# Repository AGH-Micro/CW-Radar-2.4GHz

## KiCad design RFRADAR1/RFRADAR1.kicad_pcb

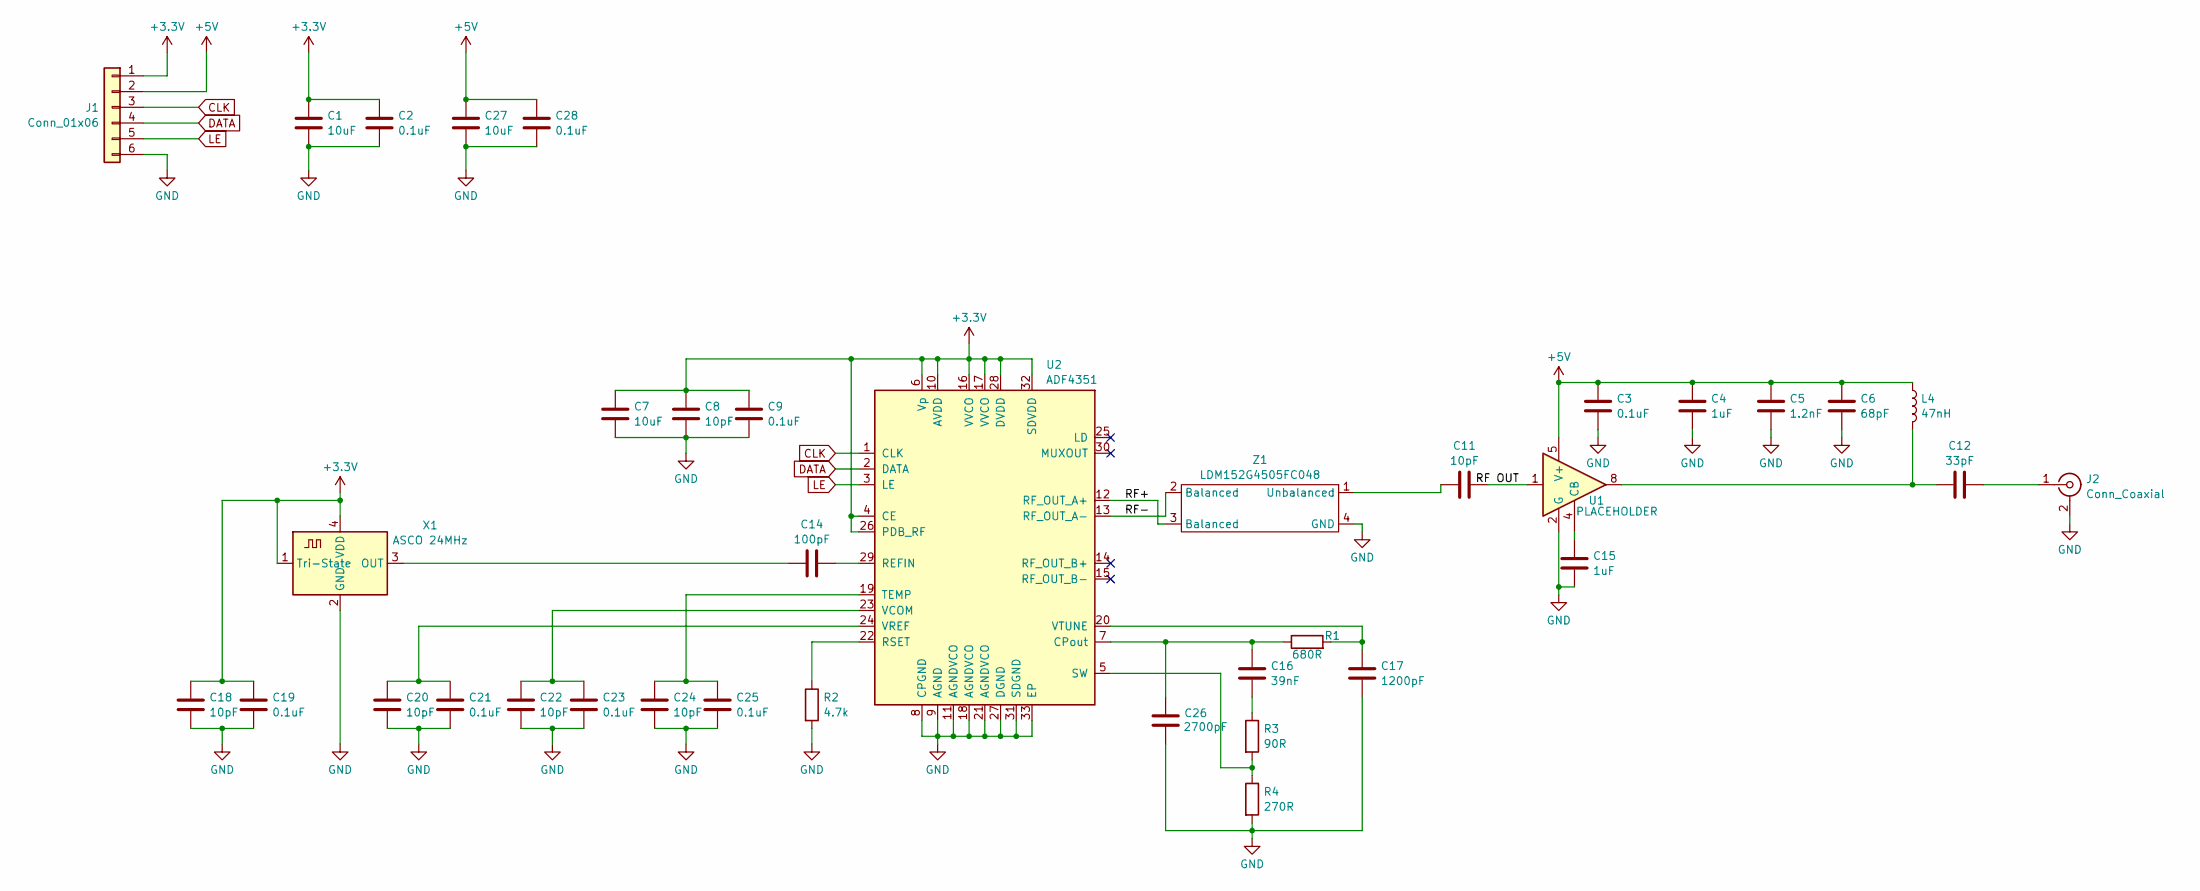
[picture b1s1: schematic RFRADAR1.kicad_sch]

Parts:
C1, C7, C27: 10uF; C_0402_1005Metric_Pad0.74x0.62mm_HandSolder
C2, C3, C9, C19, C21, C23, C25, C28: 0.1uF; C_0402_1005Metric_Pad0.74x0.62mm_HandSolder
C4, C15: 1uF; C_0402_1005Metric_Pad0.74x0.62mm_HandSolder
C5: 1.2nF; C_0402_1005Metric_Pad0.74x0.62mm_HandSolder
C6: 68pF; C_0402_1005Metric_Pad0.74x0.62mm_HandSolder
C8, C11, C18, C20, C22, C24: 10pF; C_0402_1005Metric_Pad0.74x0.62mm_HandSolder
C12: 33pF; C_0402_1005Metric_Pad0.74x0.62mm_HandSolder
C14: 100pF; C_0402_1005Metric_Pad0.74x0.62mm_HandSolder
C16: 39nF; C_0402_1005Metric_Pad0.74x0.62mm_HandSolder
C17: 1200pF; C_0402_1005Metric_Pad0.74x0.62mm_HandSolder
C26: 2700pF; C_0402_1005Metric_Pad0.74x0.62mm_HandSolder
J1: Conn_01x06; JST_PH_B6B-PH-K_1x06_P2.00mm_Vertical
J2: Conn_Coaxial; SMA_Amphenol_901-144_Vertical
L4: 47nH; L_0402_1005Metric_Pad0.77x0.64mm_HandSolder
R1: 680R; R_0402_1005Metric_Pad0.72x0.64mm_HandSolder
R2: 4.7k; R_0402_1005Metric_Pad0.72x0.64mm_HandSolder
R3: 90R; R_0402_1005Metric_Pad0.72x0.64mm_HandSolder
R4: 270R; R_0402_1005Metric_Pad0.72x0.64mm_HandSolder
U1: PLACEHOLDER; Analog_LFCSP-8-1EP_3x3mm_P0.5mm_EP1.53x1.85mm
U2: ADF4351; LFCSP-32-1EP_5x5mm_P0.5mm_EP3.25x3.25mm
X1: ASCO 24MHz; Oscillator_SMD_Abracon_ASCO-4Pin_1.6x1.2mm
Z1: LDM152G4505FC048; 4 pin 0402

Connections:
+3.3V: C1.1, C2.1, C7.1, C8.1, C9.1, C18.1, C19.1, J1.1, U2.4 (CE), U2.6 (Vp), U2.10 (AVDD), U2.16 (VVCO), U2.17 (VVCO), U2.26 (PDB_RF), U2.28 (DVDD), U2.32 (SDVDD), X1.1 (Tri-State), X1.4 (VDD)
+5V: C3.1, C4.1, C5.1, C6.1, C27.1, C28.1, J1.2, L4.1, U1.5 (V+)
/RF OUT: C11.2, U1.1
/RF+: U2.12 (RF_OUT_A+), Z1.3 (Balanced)
/RF-: U2.13 (RF_OUT_A-), Z1.2 (Balanced)
CLK: J1.3, U2.1 (CLK)
DATA: J1.4, U2.2 (DATA)
GND: C1.2, C2.2, C3.2, C4.2, C5.2, C6.2, C7.2, C8.2, C9.2, C15.2, C17.2, C18.2, C19.2, C20.2, C21.2, C22.2, C23.2, C24.2, C25.2, C26.2, C27.2, C28.2, J1.6, J2.2 (Ext), R2.2, R4.2, U1.2 (G), U2.8 (CPGND), U2.9 (AGND), U2.11 (AGNDVCO), U2.18 (AGNDVCO), U2.21 (AGNDVCO), U2.27 (DGND), U2.31 (SDGND), U2.33 (EP), X1.2 (GND), Z1.4 (GND)
LE: J1.5, U2.3 (LE)
unnamed: C12.1, L4.2, U1.8
unnamed: C16.2, R3.1
unnamed: C12.2, J2.1 (In)
unnamed: C15.1, U1.4 (CB)
unnamed: C16.1, C26.1, R1.1, U2.7 (CPout)
unnamed: C14.2, U2.29 (REFIN)
unnamed: R2.1, U2.22 (RSET)
unnamed: R3.2, R4.1, U2.5 (SW)
unnamed: C24.1, C25.1, U2.19 (TEMP)
unnamed: C22.1, C23.1, U2.23 (VCOM)
unnamed: C20.1, C21.1, U2.24 (VREF)
unnamed: C17.1, R1.2, U2.20 (VTUNE)
unnamed: C14.1, X1.3 (OUT)
unnamed: C11.1, Z1.1 (Unbalanced)

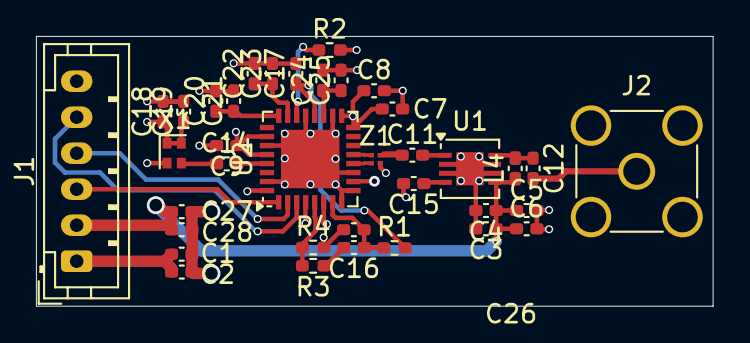
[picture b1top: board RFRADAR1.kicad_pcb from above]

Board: 4 copper layers, 37.6 x 15.0 mm, 37 parts (0 on the bottom side), 23 nets.

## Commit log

2025-05-04 Added basic file as example (Warning not a real main.py or something like that) for future referance
2025-05-07 VCO - WIP
